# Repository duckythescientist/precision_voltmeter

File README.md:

# Precision Voltmeter

Partly based off of the Scullcom millivolt meter: http://www.scullcom.uk/design-build-6%c2%bd-digit-millivolt-meter-part-1/

## Serial comms

```
Commands:
    h    - Print this help
    ?    - Print version and date
    r    - Toggle live readout over serial
    p    - Print calibration
    z    - Calibrate at 0V (inputs shorted)
    c... - Calibrate for a specific range and value

Calibration:
    c[n]:[f]  - Calibrates for range [n] with external applied voltage [f]
    Range:
        0: x1 LV
        1: x10
        2: x100
        3: x1000
    Example: to calibrate the x10 range (HV input) with a 4.123V reference,
        the command would be `c1:4.123`
```

# Improvement notes

I added an opto-isolated serial output and spent a weekend tearing down and building back up the circuit. I don't think it's going to get much better than it is (or already was). Without ESD/EMI and environmental noise, the noise in the readings is on the same order of magnitude that I'd expect from thermal noise of a 1Meg resistor. Assuming that my napkin math is correct. Also, the constant offset that I'm seeing is also on the order of what's to be expected with the input bias current of the LTC2057 and a 1Meg resistor. I guess it's just up to software corrections. Still getting around 19-20 usable bits from the ADC. I'm calling that a win.

Environmental noise is still a big issue. Stddev of the readings lowers by an order of magnitude if I sit perfectly still.

# Notes for Future Versions and Improvements

## Issues

The LTC2057 has a common-mode input range from 0.1V below V- to 1.5V _below_ V+. Meaning that with a -2.5V,+5V supply, I can only buffer signals up to 3.5V technically. I'm seeing some sort of latchup-type behavior at around 4.2V. I've bodged in a 6.8V supply rail to the op-amp.

## Bodges

The sampling of the ADC is rather noisy. Adding filter capacitors right at the input and the vref seem to help. Reduced the resistor between the buffer and the ADC to 2.2k. May want to go lower? I'm currently at 100R series from the buffer to the ADC and a 2.2nF cap to gnd.

Adding extra voltage regulator to drive the op-amp positive rail at around 6.8V to give enough common-mode headroom to buffer a full input swing to the ADC.

## Future

The x10 mode presents around a 1Meg input impedance to the op-amp this combined with the couple hundred pA of input bias and offset results in a couple hundred microvolts of DC offset. This has a minimal temperature coefficient up to about 75C but does have a common-mode voltage dependence. I'm not sure what to do to fix it.

A 1Meg input impedance may be the way to go.

For lower noise, it may be nice to try LT3094 and LT3042 for post switching converter regulation. The switching regulator. However, the voltage lines look pretty clean right now. Also, these regulators are pretty expensive and are DFN packages. UPDATE: replacing the switching regulator with batteries didn't measurably reduce the noise. The current design is good enough.

A metal enclosure and/or more shielding could maybe help with environmental noise.

I need a buffer amp for the output of my Kelvin-Varley divider. Or I need a voltage reference below about 4V to calibrate the x1 range. This is a lab problem and not a problem of the voltmeter.

I need to investigate Barbouri's v2 design and see if there is anything worth adding to my design.

# References

## App Notes

Shielding and guarding: https://www.analog.com/media/en/technical-documentation/application-notes/41727248an_347.pdf

Staying well grounded: https://www.analog.com/en/analog-dialogue/articles/staying-well-grounded.html

Millivolt meter PCB: https://www.barbouri.com/2016/05/26/millivolt-meter/ and https://www.barbouri.com/2019/08/07/millivolt-meter-version-2/

EMI filtering for DC-DC converters: https://www.ti.com/lit/an/snva489c/snva489c.pdf

Ferrite beads demystified: https://www.analog.com/en/analog-dialogue/articles/ferrite-beads-demystified.html

Shielding and guarding: https://www.analog.com/media/en/technical-documentation/application-notes/41727248an_347.pdf

PCB guidelines for reduced EMI: https://www.ti.com/lit/an/szza009/szza009.pdf

Overvoltage protection for sensitive amplifier applications: https://www.maximintegrated.com/en/design/technical-documents/app-notes/4/4035.html

Switching low-level signals to a DMM: https://www.ni.com/en-us/innovations/white-papers/06/switching-low-level-signals-to-a-dmm.html

## Datasheets

Voltage reference, ADR4540, used in Scullcom's meter: https://www.analog.com/media/en/technical-documentation/data-sheets/ADR4520_4525_4530_4533_4540_4550.pdf

Voltage reference, MAX6126, used in my meter, kelvin connections: https://datasheets.maximintegrated.com/en/ds/MAX6126.pdf

Negative adjustable voltage regulator, LM337L: https://www.ti.com/lit/ds/symlink/lm337l.pdf

HV low noise zero-drift op-amp, LTC2057, used in my meter: https://www.analog.com/media/en/technical-documentation/data-sheets/2057f.pdf

Zero-drift single-supply rail-to-rail op-amp, AD8628, used in Scullcom's meter: https://www.analog.com/media/en/technical-documentation/data-sheets/AD8628_8629_8630.pdf

ADC 24-bit, LTC2400: https://www.analog.com/media/en/technical-documentation/data-sheets/2400fa.pdf

SPI digital isolator, ADuM3152: https://www.analog.com/media/en/technical-documentation/data-sheets/ADuM3151_3152_3153.pdf

ATmega32U4: https://ww1.microchip.com/downloads/en/DeviceDoc/Atmel-7766-8-bit-AVR-ATmega16U4-32U4_Datasheet.pdf

## Software

64-bit floating point library for AVR-8: https://fp64lib.org/documentation/fp64lib-library-reference/ and https://github.com/fp64lib/fp64lib

MAX7219 7-seg LED driver library: https://github.com/JemRF/max7219

PinChangeInterrupt: https://github.com/NicoHood/PinChangeInterrupt

Statistics library for Arduino: https://github.com/RobTillaart/Statistic

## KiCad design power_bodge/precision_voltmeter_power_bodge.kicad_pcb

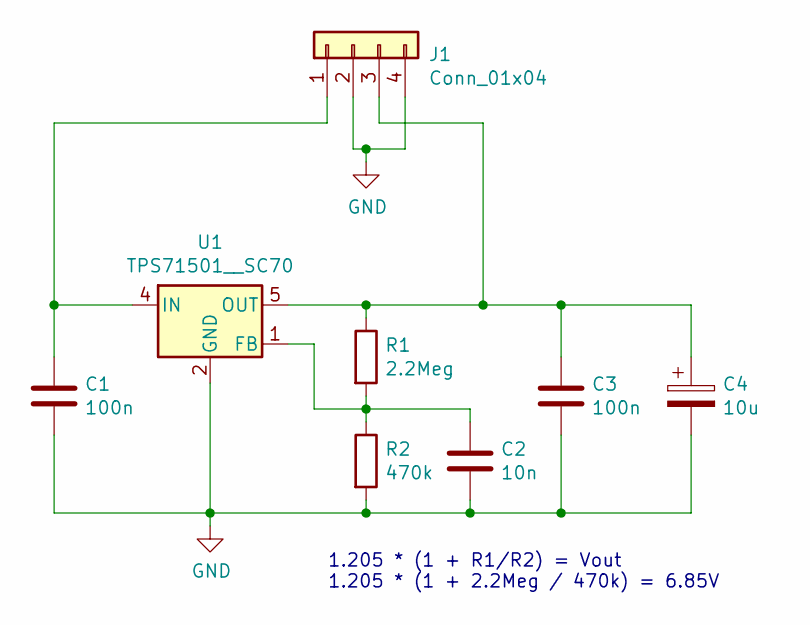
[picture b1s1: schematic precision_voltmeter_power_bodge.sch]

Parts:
C1, C3: 100n; C_0805_2012Metric_Pad1.18x1.45mm_HandSolder
C2: 10n; C_0805_2012Metric_Pad1.18x1.45mm_HandSolder
C4: 10u; C_0805_2012Metric_Pad1.18x1.45mm_HandSolder
J1: Conn_01x04; PinHeader_1x04_P2.54mm_Vertical
R1: 2.2Meg; R_0805_2012Metric_Pad1.20x1.40mm_HandSolder
R2: 470k; R_0805_2012Metric_Pad1.20x1.40mm_HandSolder
U1: TPS71501__SC70; SOT-353_SC-70-5

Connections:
GND: C1.2, C2.2, C3.2, C4.2, J1.2, J1.4, R2.2, U1.2 (GND)
unnamed: C1.1, J1.1, U1.4 (IN)
unnamed: C2.1, R1.2, R2.1, U1.1 (FB)
unnamed: C3.1, C4.1, J1.3, R1.1, U1.5 (OUT)

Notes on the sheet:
1.205 * (1 + R1/R2) = Vout 1.205 * (1 + 2.2Meg / 470k) = 6.85V

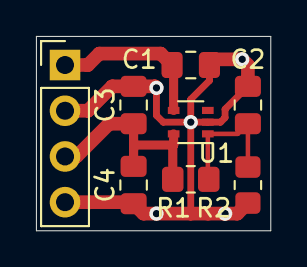
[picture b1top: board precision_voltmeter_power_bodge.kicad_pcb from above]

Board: 2 copper layers, 13.0 x 10.8 mm, 8 parts (0 on the bottom side), 4 nets.

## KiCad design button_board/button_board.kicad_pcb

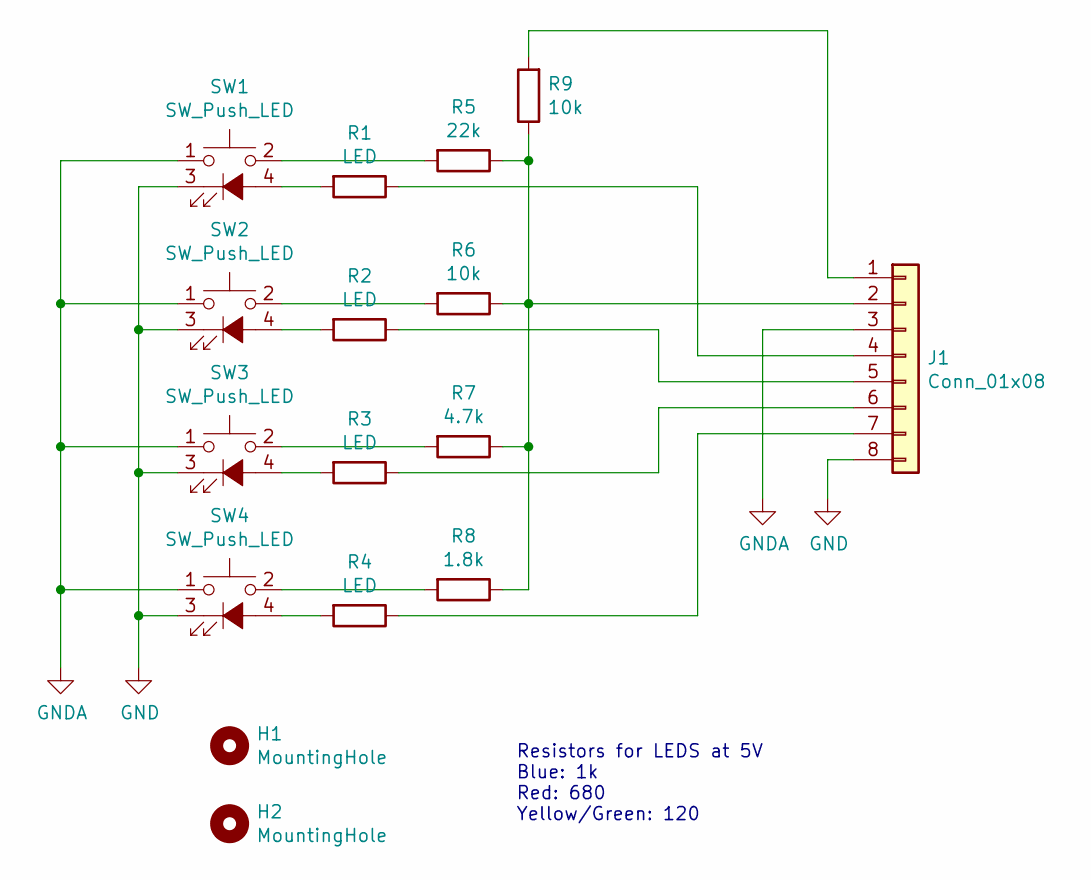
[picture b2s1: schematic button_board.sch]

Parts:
H1, H2: MountingHole; MountingHole_2.7mm_M2.5
J1: Conn_01x08; PinHeader_1x08_P2.54mm_Vertical
R1, R2, R3, R4: LED; R_0805_2012Metric_Pad1.20x1.40mm_HandSolder
R5: 22k; R_0805_2012Metric_Pad1.20x1.40mm_HandSolder
R6, R9: 10k; R_0805_2012Metric_Pad1.20x1.40mm_HandSolder
R7: 4.7k; R_0805_2012Metric_Pad1.20x1.40mm_HandSolder
R8: 1.8k; R_0805_2012Metric_Pad1.20x1.40mm_HandSolder
SW1, SW2, SW3, SW4: SW_Push_LED; tactile-push-button-illuminated_ILS_TA180

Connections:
GND: J1.8, SW1.3 (K), SW2.3 (K), SW3.3 (K), SW4.3 (K)
GNDA: J1.3, SW1.1, SW2.1, SW3.1, SW4.1
unnamed: J1.1, R9.2
unnamed: J1.2, R5.1, R6.1, R7.1, R8.1, R9.1
unnamed: J1.4, R1.1
unnamed: J1.5, R2.1
unnamed: J1.6, R3.1
unnamed: J1.7, R4.1
unnamed: R1.2, SW1.4 (A)
unnamed: R2.2, SW2.4 (A)
unnamed: R3.2, SW3.4 (A)
unnamed: R4.2, SW4.4 (A)
unnamed: R5.2, SW1.2
unnamed: R6.2, SW2.2
unnamed: R7.2, SW3.2
unnamed: R8.2, SW4.2

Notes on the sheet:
Resistors for LEDS at 5V Blue: 1k Red: 680 Yellow/Green: 120

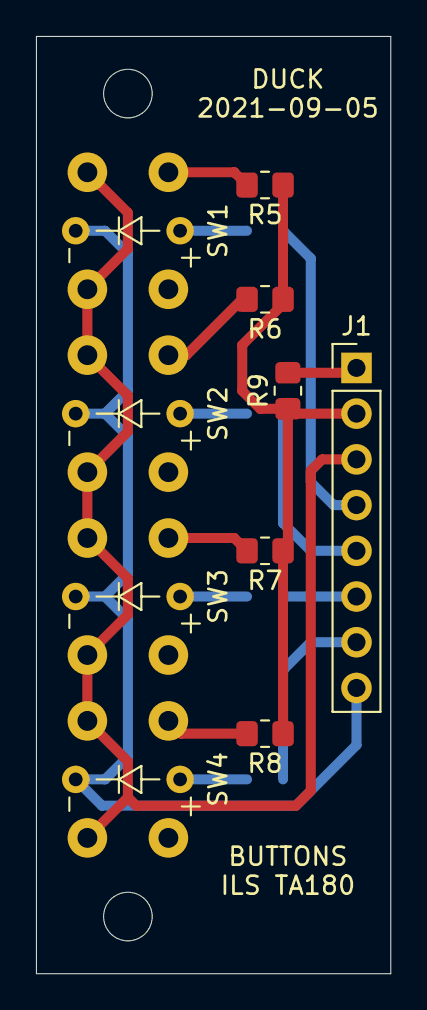
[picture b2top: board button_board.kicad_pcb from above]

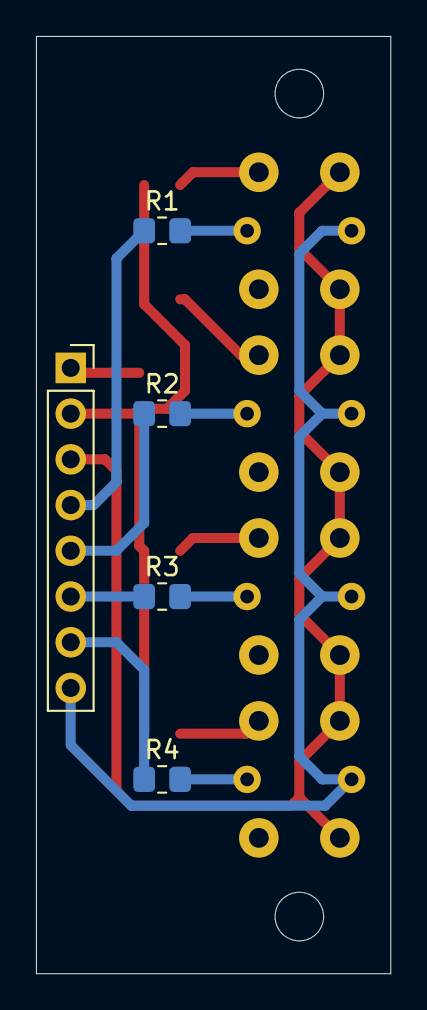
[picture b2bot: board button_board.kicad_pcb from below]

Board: 2 copper layers, 19.7 x 52.1 mm, 16 parts (4 on the bottom side), 16 nets.

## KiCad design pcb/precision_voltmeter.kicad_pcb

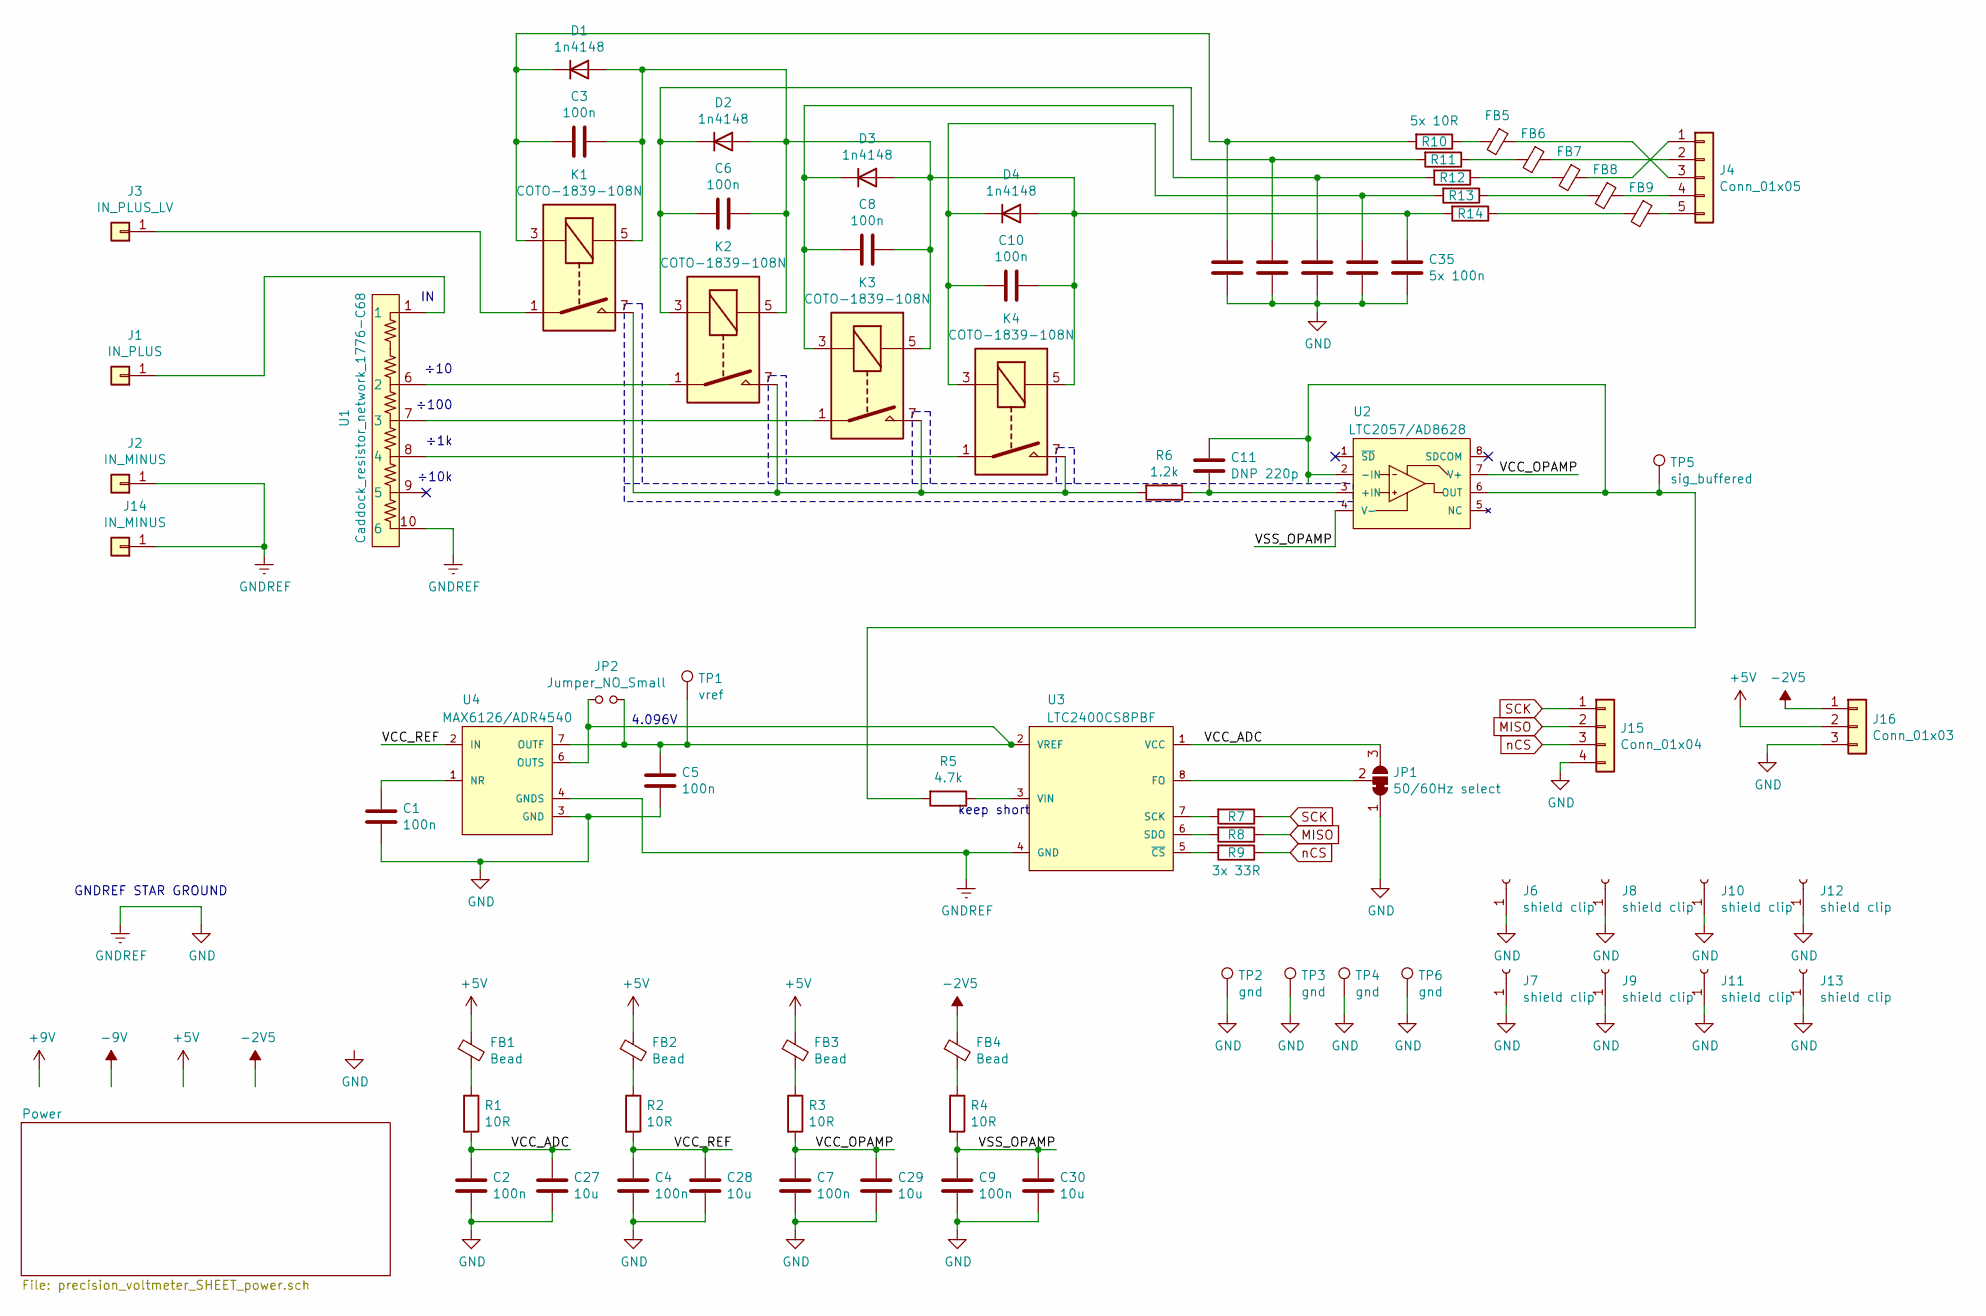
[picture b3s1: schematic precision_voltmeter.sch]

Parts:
C1, C2, C3, C4, C5, C6, C7, C8, C9, C10, C31, C32, C33, C34: 100n; C_0805_2012Metric_Pad1.18x1.45mm_HandSolder
C11: DNP 220p; C_0805_2012Metric_Pad1.18x1.45mm_HandSolder
C27, C28, C29, C30: 10u; C_0805_2012Metric_Pad1.18x1.45mm_HandSolder
C35: 5x 100n; C_0805_2012Metric_Pad1.18x1.45mm_HandSolder
D1, D2, D3, D4: 1n4148; D_SOD-123F
FB1, FB2, FB3, FB4, FB5, FB6, FB7, FB8, FB9: Bead; L_0805_2012Metric_Pad1.05x1.20mm_HandSolder
J1: IN_PLUS; Pin_D1.3mm_L11.0mm
J2, J14: IN_MINUS; Pin_D1.3mm_L11.0mm
J3: IN_PLUS_LV; Pin_D1.3mm_L11.0mm
J4: Conn_01x05; PinHeader_1x05_P2.54mm_Vertical
J6, J7, J8, J9, J10, J11, J12, J13: shield clip; smt_rfi_clip_S2711-46R
J15: Conn_01x04; PinHeader_1x04_P2.54mm_Vertical
J16: Conn_01x03; PinHeader_1x03_P2.54mm_Vertical
JP1: 50/60Hz select; SolderJumper-3_P1.3mm_Bridged12_RoundedPad1.0x1.5mm
JP2: Jumper_NO_Small; SolderJumper-2_P1.3mm_Open_RoundedPad1.0x1.5mm
K1, K2, K3, K4: COTO-1839-108N; Relay_SPST_StandexMeder_SIL_Form1A
R1, R2, R3, R4, R11, R12, R13, R14: 10R; R_0805_2012Metric_Pad1.20x1.40mm_HandSolder
R5: 4.7k; R_0805_2012Metric_Pad1.20x1.40mm_HandSolder
R6: 1.2k; R_0805_2012Metric_Pad1.20x1.40mm_HandSolder
R7, R8: 33; R_0805_2012Metric_Pad1.20x1.40mm_HandSolder
R9: 3x 33R; R_0805_2012Metric_Pad1.20x1.40mm_HandSolder
R10: 5x 10R; R_0805_2012Metric_Pad1.20x1.40mm_HandSolder
TP1: vref; TestPoint_THTPad_D2.0mm_Drill1.0mm
TP2, TP3, TP4, TP6: gnd; TestPoint_THTPad_D2.0mm_Drill1.0mm
TP5: sig_buffered; TestPoint_THTPad_D2.0mm_Drill1.0mm
U1: Caddock_resistor_network_1776-C68; R_Array_SIP10-6
U2: LTC2057/AD8628; SOIC-8_3.9x4.9mm_P1.27mm; MANUFACTURER_PART_NUMBER ltc2057is8#trpbf
U3: LTC2400CS8PBF; SOIC-8_3.9x4.9mm_P1.27mm; MPN LTC2400CS8#PBF
U4: MAX6126/ADR4540; SOIC-8_3.9x4.9mm_P1.27mm

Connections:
+5V: FB1.1, FB2.1, FB3.1, J16.2; also elsewhere on the board
-2V5: FB4.1, J16.1; also elsewhere on the board
/VCC_ADC: C2.1, C27.1, JP1.3 (B), R1.2, U3.1 (VCC)
/VCC_OPAMP: C7.1, C29.1, R3.2, U2.7 (V+)
/VCC_REF: C4.1, C28.1, R2.2, U4.2 (IN)
/VSS_OPAMP: C9.1, C30.1, R4.2, U2.4 (V-)
GND: C1.2, C2.2, C4.2, C5.2, C7.2, C9.2, C27.2, C28.2, C29.2, C30.2, C31.1, C32.1, C33.1, C34.1, C35.1, J2.1, J6.1, J7.1, J8.1, J9.1, J10.1, J11.1, J12.1, J13.1, J14.1, J15.4, J16.3, JP1.1 (A), TP2.1, TP3.1, TP4.1, TP6.1, U1.10 (6), U3.4 (GND), U4.3 (GND), U4.4 (GNDS); also elsewhere on the board
MISO: J15.2, R8.1; also elsewhere on the board
unnamed: C1.1, U4.1 (NR)
unnamed: C3.2, C31.2, D1.1 (K), K1.3, R10.2
unnamed: C5.1, JP2.1, JP2.2, TP1.1, U3.2 (VREF), U4.6 (OUTS), U4.7 (OUTF)
unnamed: C3.1, C6.1, C8.1, C10.1, C35.2, D1.2 (A), D2.2 (A), D3.2 (A), D4.2 (A), K1.5, K2.5, K3.5, K4.5, R14.2
unnamed: C10.2, C34.2, D4.1 (K), K4.3, R13.2
unnamed: C11.1, R5.2, TP5.1, U2.2 (-IN), U2.6 (OUT)
unnamed: C11.2, R6.1, U2.3 (+IN)
unnamed: C6.2, C32.2, D2.1 (K), K2.3, R11.2
unnamed: C8.2, C33.2, D3.1 (K), K3.3, R12.2
unnamed: FB1.2, R1.1
unnamed: FB2.2, R2.1
unnamed: FB3.2, R3.1
unnamed: FB4.2, R4.1
unnamed: FB5.1, J4.3
unnamed: FB5.2, R10.1
unnamed: FB6.1, J4.2
unnamed: FB6.2, R11.1
unnamed: FB7.1, J4.1
unnamed: FB7.2, R12.1
unnamed: FB8.1, J4.4
unnamed: FB8.2, R13.1
unnamed: FB9.1, J4.5
unnamed: FB9.2, R14.1
unnamed: J1.1, U1.1
unnamed: J3.1, K1.1
unnamed: JP1.2 (C), U3.8 (FO)
unnamed: K1.7, K2.7, K3.7, K4.7, R6.2
unnamed: K2.1, U1.6 (2)
unnamed: K3.1, U1.7 (3)
unnamed: K4.1, U1.8 (4)
unnamed: R5.1, U3.3 (VIN)
unnamed: R7.2, U3.7 (SCK)
unnamed: R8.2, U3.6 (SDO)
unnamed: R9.2, U3.5 (~CS)
SCK: J15.1, R7.1; also elsewhere on the board
nCS: J15.3, R9.1; also elsewhere on the board

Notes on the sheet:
keep short
÷10
÷100
÷1k
÷10k
4.096V
GNDREF STAR GROUND

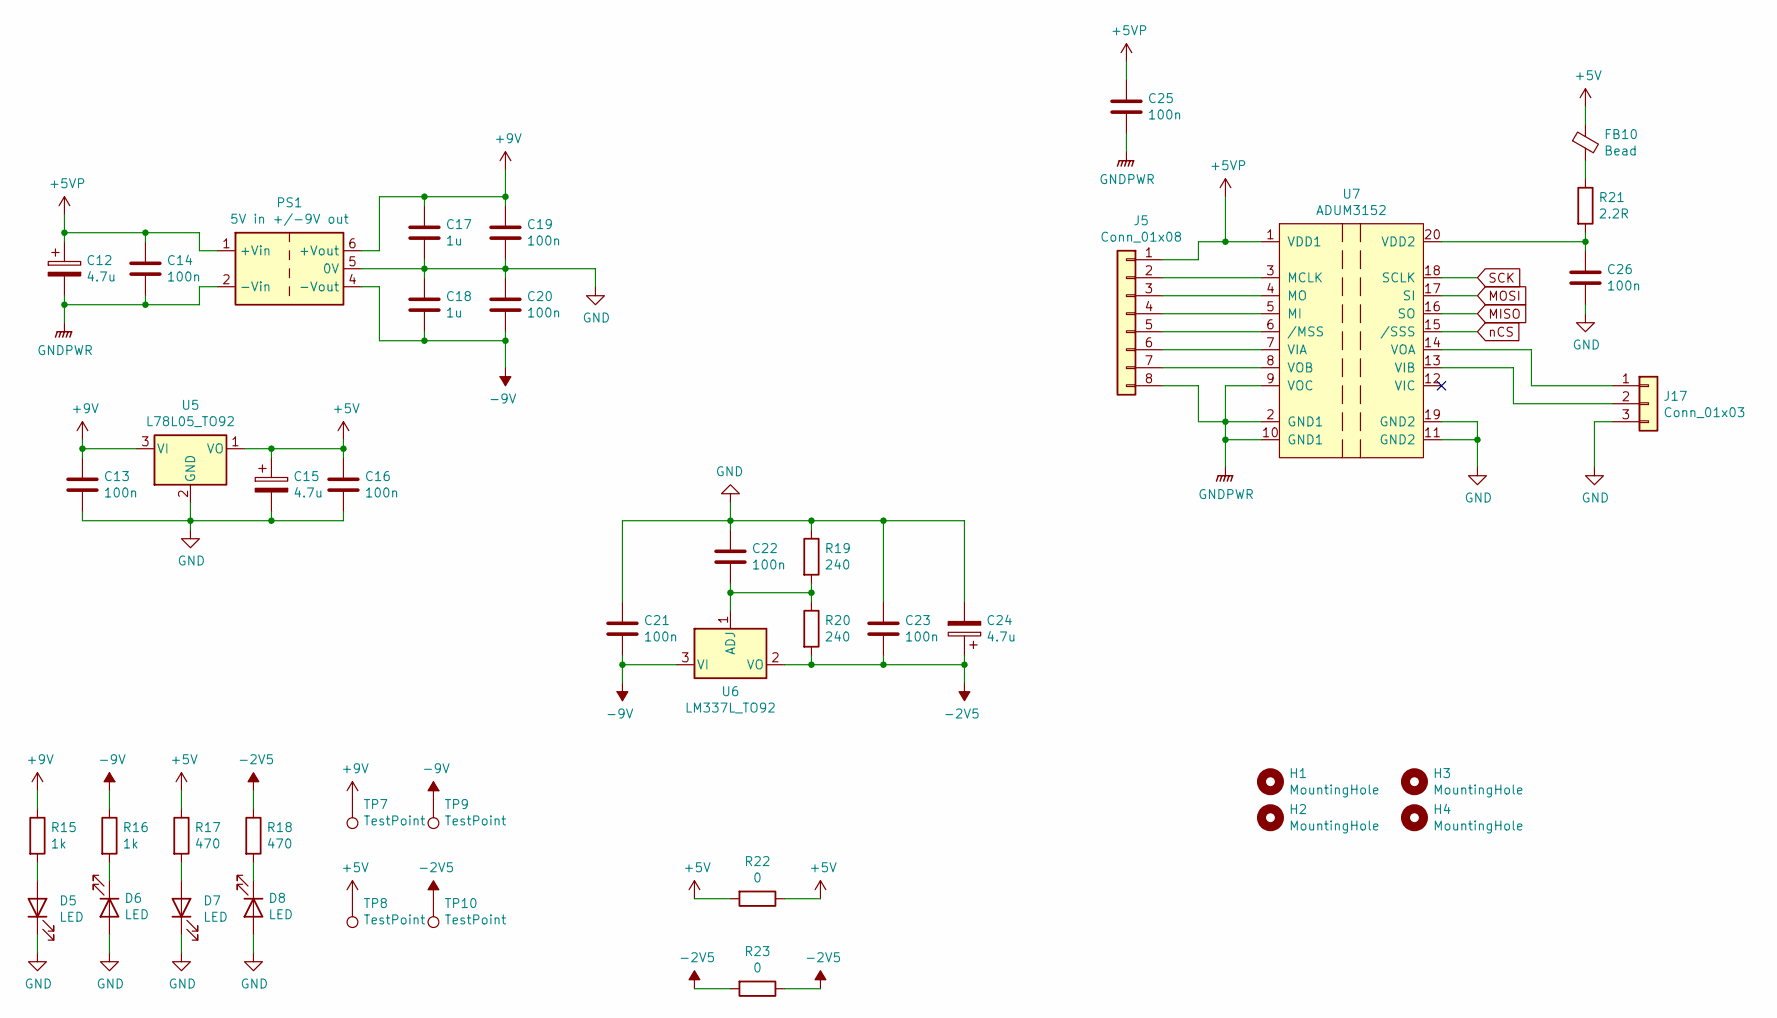
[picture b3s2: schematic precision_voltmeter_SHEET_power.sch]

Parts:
C12, C15, C24: 4.7u; CP_EIA-3528-12_Kemet-T_Pad1.50x2.35mm_HandSolder
C13, C14, C16, C19, C20, C21, C22, C23, C25, C26: 100n; C_0805_2012Metric_Pad1.18x1.45mm_HandSolder
C17, C18: 1u; C_0805_2012Metric_Pad1.18x1.45mm_HandSolder
D5, D6, D7, D8: LED; LED_0805_2012Metric_Pad1.15x1.40mm_HandSolder
FB10: Bead; L_0805_2012Metric_Pad1.05x1.20mm_HandSolder
H1, H2, H3, H4: MountingHole; MountingHole_3.2mm_M3
J5: Conn_01x08; PinHeader_1x08_P2.54mm_Vertical
J17: Conn_01x03; PinHeader_1x03_P2.54mm_Vertical
PS1: 5V in +/-9V out; Converter_DCDC_XP_POWER-IAxxxxS_THT
R15, R16: 1k; R_0805_2012Metric_Pad1.20x1.40mm_HandSolder
R17, R18: 470; R_0805_2012Metric_Pad1.20x1.40mm_HandSolder
R19, R20: 240; R_0805_2012Metric_Pad1.20x1.40mm_HandSolder
R21: 2.2R; R_0805_2012Metric_Pad1.20x1.40mm_HandSolder
R22, R23: 0; R_Axial_DIN0204_L3.6mm_D1.6mm_P5.08mm_Horizontal
TP7, TP8, TP9, TP10: TestPoint; TestPoint_THTPad_D2.0mm_Drill1.0mm
U5: L78L05_TO92; TO-92_Inline
U6: LM337L_TO92; TO-92_Inline
U7: ADUM3152; SSOP-20_5.3x7.2mm_P0.65mm

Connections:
+5V: C15.1, C16.1, FB10.1, R17.1, R22.1, R22.2, TP8.1, U5.1 (VO); also elsewhere on the board
+5VP: C12.1, C14.1, C25.1, J5.1, PS1.1 (+Vin), U7.1 (VDD1)
+9V: C13.1, C17.1, C19.1, PS1.6 (+Vout), R15.1, TP7.1, U5.3 (VI)
-2V5: C23.2, C24.1, R18.1, R20.2, R23.1, R23.2, TP10.1, U6.2 (VO); also elsewhere on the board
-9V: C18.1, C20.1, C21.2, PS1.4 (-Vout), R16.1, TP9.1, U6.3 (VI)
GND: C13.2, C15.2, C16.2, C17.2, C18.2, C19.2, C20.2, C21.1, C22.1, C23.1, C24.2, C26.2, D5.1 (K), D6.2 (A), D7.1 (K), D8.2 (A), J17.3, PS1.5 (0V), R19.1, U5.2 (GND), U7.11 (GND2), U7.19 (GND2); also elsewhere on the board
GNDPWR: C12.2, C14.2, C25.2, J5.8, PS1.2 (-Vin), U7.2 (GND1), U7.9 (VOC), U7.10 (GND1)
MISO: U7.16 (SO); also elsewhere on the board
MOSI: U7.17 (SI)
unnamed: C22.2, R19.2, R20.1, U6.1 (ADJ)
unnamed: C26.1, R21.2, U7.20 (VDD2)
unnamed: D5.2 (A), R15.2
unnamed: D6.1 (K), R16.2
unnamed: D7.2 (A), R17.2
unnamed: D8.1 (K), R18.2
unnamed: FB10.2, R21.1
unnamed: J5.2, U7.3 (MCLK)
unnamed: J5.3, U7.4 (MO)
unnamed: J5.4, U7.5 (MI)
unnamed: J5.5, U7.6 (/MSS)
unnamed: J5.6, U7.7 (VIA)
unnamed: J5.7, U7.8 (VOB)
unnamed: J17.1, U7.14 (VOA)
unnamed: J17.2, U7.13 (VIB)
SCK: U7.18 (SCLK); also elsewhere on the board
nCS: U7.15 (/SSS); also elsewhere on the board

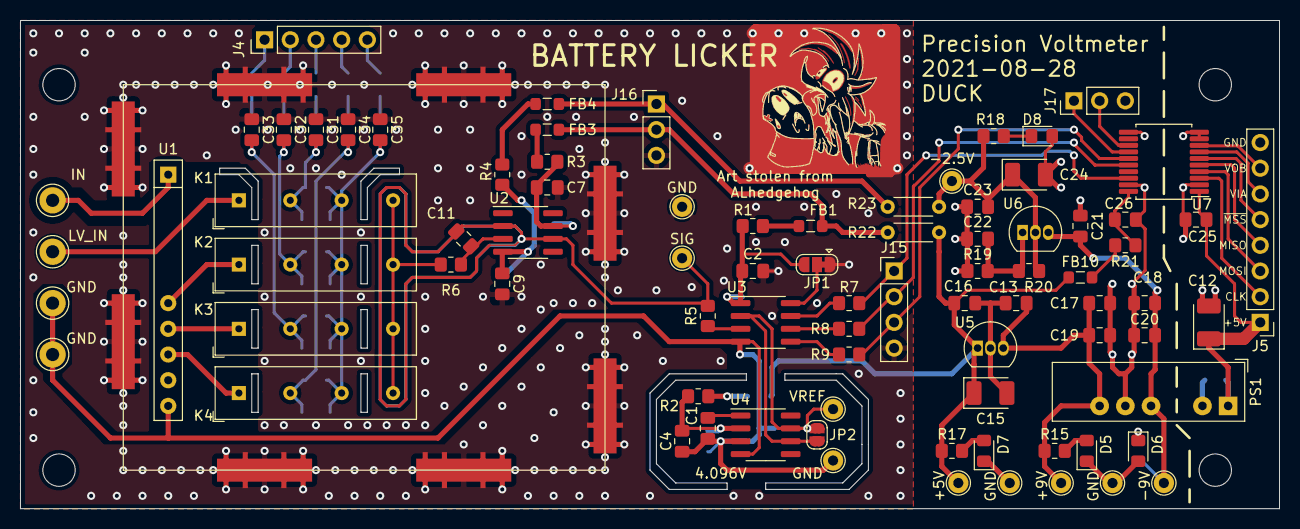
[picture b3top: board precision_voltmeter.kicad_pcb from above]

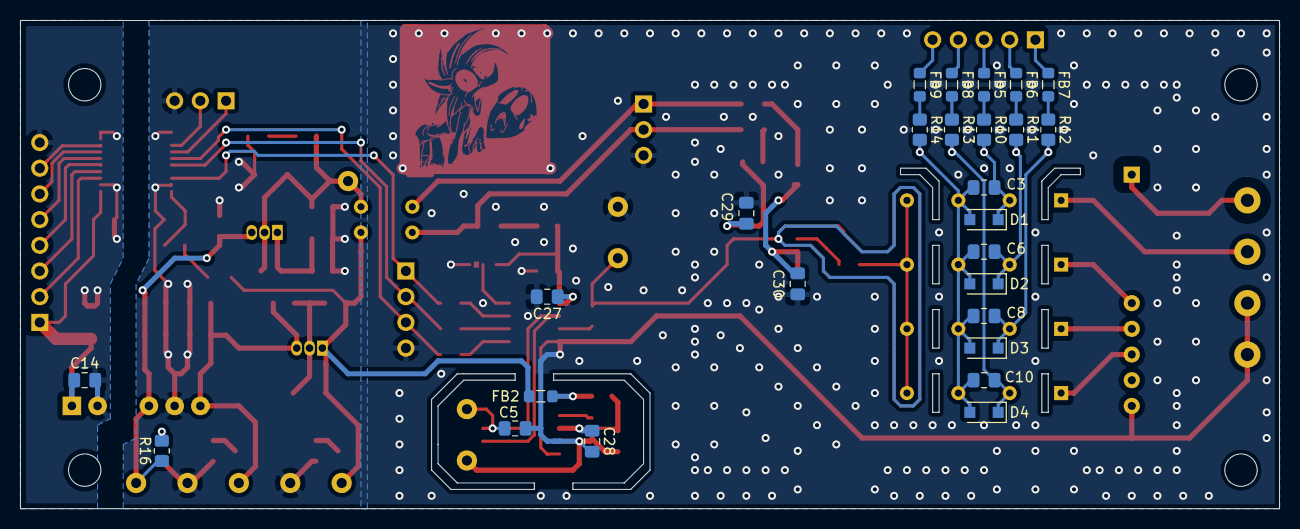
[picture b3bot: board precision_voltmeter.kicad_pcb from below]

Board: 2 copper layers, 124.5 x 48.3 mm, 121 parts (26 on the bottom side), 63 nets.

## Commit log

2021-09-22 Add initial working files
2021-09-25 SCH ONLY, add bodge filter caps
2021-09-25 Add cal printing and button combo
2021-09-25 Add button board files
2021-09-26 Add power bodge board
2021-09-26 Add calibration (for non-zero) and super slow averaging
    Also fix a bug with the display maths
2022-02-27 Add reading stability indication
2022-02-27 Update with optical serial
2022-02-27 Add more serial changes
2022-03-07 Add test script
2022-03-07 Add notes about tests
2022-03-07 Improve serial UI
2022-03-07 Update with last of recordings
2022-03-07 Make exiting from under/over error more graceful
2022-03-07 Update readme with results of noise testing
2022-03-07 Add 3d printable vref cover
